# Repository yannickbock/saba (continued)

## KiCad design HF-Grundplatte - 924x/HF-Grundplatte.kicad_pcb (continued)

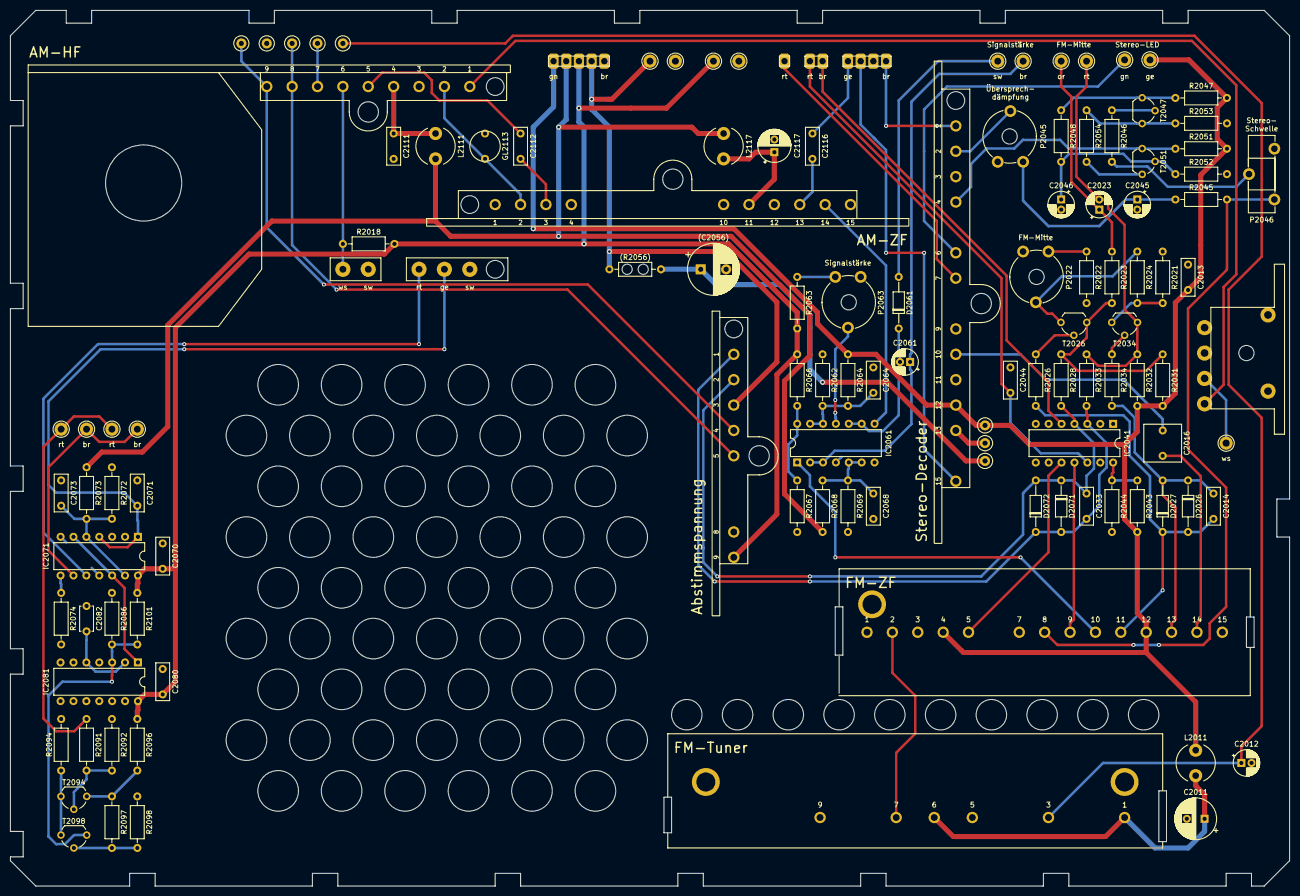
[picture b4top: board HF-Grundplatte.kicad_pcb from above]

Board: 2 copper layers, 252.0 x 172.5 mm, 120 parts (0 on the bottom side), 79 nets.

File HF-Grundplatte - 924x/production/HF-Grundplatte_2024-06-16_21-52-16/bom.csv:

Designator,Footprint,Quantity,Value,LCSC Part #
"_2, ",e9502d42-3ef4-4c54-9284-00e123373677,2,,
C2011,CP_Radial_D8.0mm_P3.50mm,1,220µ,
C2012,CP_Radial_D5.0mm_P2.00mm,1,2.2µ,
"C2013, C2014, C2044, C2064, C2068, C2070, C2071, C2073, C2080, C2111, C2112, C2116",C_Rect_L7.2mm_W2.5mm_P5.00mm_FKS2_FKP2_MKS2_MKP2,12,100n,
C2016,C_Rect_L7.2mm_W7.2mm_P5.00mm_FKS2_FKP2_MKS2_MKP2,1,2.2µ,
"C2023, C2061",CP_Radial_D5.0mm_P2.00mm,2,47µ,
C2033,C_Rect_L7.2mm_W2.5mm_P5.00mm_FKS2_FKP2_MKS2_MKP2,1,680n,
C2045,CP_Radial_D5.0mm_P2.00mm,1,22µ,
C2046,CP_Radial_D5.0mm_P2.00mm,1,4.7µ,
C2056,CP_Radial_D10.0mm_P5.00mm,1,100µ,
C2082,C_Disc_D4.7mm_W2.5mm_P5.00mm,1,22n,
C2117,CP_Radial_D6.3mm_P2.50mm,1,100µ,
"D2026, D2027, D2071, D2072",D_DO-35_SOD27_P10.16mm_Horizontal,4,1N4148,
D2061,D_DO-35_SOD27_P10.16mm_Horizontal,1,AA143,
GL2113,Glimmlampe,1,110V/0.6mA,
"IC2041, IC2061, IC2071",DIP-14_W7.62mm,3,4016,
IC2081,DIP-14_W7.62mm,1,4013,
J1,FM-Tuner,1,FM-Tuner,
"J10, J13, J26, J27, J9",Pin_D1.3mm_L11.0mm,5,br,
J11,Conn_01x04,1,NF,
J12,Conn_01x05,1,Power,
"J14, J34, J35, J36, J37",Pin_D1.3mm_L11.0mm,5,sw,
J15,Pin_D1.3mm_L11.0mm,1,rt,
J16,Pin_D1.3mm_L11.0mm,1,or,
J17,Pin_D1.3mm_L11.0mm,1,gn,
J18,Pin_D1.3mm_L11.0mm,1,ge,
J19,Conn_01x01,1,rt,
J2,AM-HF,1,AM-HF,
J20,SolderPads_Bridge_01x03_2.5mm,1,Conn_01x03,
"J21, J22, J23, J24, J25",TestPoint_Loop_D1.80mm_Drill1.0mm_Beaded,5,rt,
J28,Conn_01x02_5mm,1,Conn_01x02,
J29,Conn_01x03_5mm,1,Conn_01x03,
J3,AM-ZF,1,AM-ZF,
J30,Conn_01x02,1,Conn_01x02,
J4,Stereo-Decoder,1,~,
J5,Abstimmspannung,1,~,
J6,FM-ZF,1,FM-ZF,
J7,AM-Antenne,1,Antenne,
J8,Pin_D1.3mm_L11.0mm,1,Conn_01x01,
"L2011, L2111, L2117",L_Radial_D7.5mm_P5.00mm_Fastron_07P,3,1000µH,
P2022,Potentiometer_Piher_PT-10-V10_Vertical,1,2.5k,
P2045,Potentiometer_Piher_PT-10-V10_Vertical,1,25k,
P2046,Potentiometer_Piher_PT-15-H05_Horizontal,1,100k,
P2063,Potentiometer_Piher_PT-10-V10_Vertical,1,10k,
R2018,R_Axial_DIN0207_L6.3mm_D2.5mm_P10.16mm_Horizontal,1,47k,
"R2021, R2031, R2032",R_Axial_DIN0207_L6.3mm_D2.5mm_P10.16mm_Horizontal,3,3.9k,
R2022,R_Axial_DIN0207_L6.3mm_D2.5mm_P10.16mm_Horizontal,1,2.7k,
"R2023, R2048, R2097",R_Axial_DIN0207_L6.3mm_D2.5mm_P10.16mm_Horizontal,3,15k,
R2024,R_Axial_DIN0207_L6.3mm_D2.5mm_P10.16mm_Horizontal,1,1k,
"R2026, R2034, R2047, R2052, R2098",R_Axial_DIN0207_L6.3mm_D2.5mm_P10.16mm_Horizontal,5,22k,
"R2028, R2033, R2045, R2067",R_Axial_DIN0207_L6.3mm_D2.5mm_P10.16mm_Horizontal,4,10k,
R2043,R_Axial_DIN0207_L6.3mm_D2.5mm_P10.16mm_Horizontal,1,2.2k,
R2044,R_Axial_DIN0207_L6.3mm_D2.5mm_P10.16mm_Horizontal,1,12k,
"R2046, R2066, R2086",R_Axial_DIN0207_L6.3mm_D2.5mm_P10.16mm_Horizontal,3,4.7k,
"R2051, R2101",R_Axial_DIN0207_L6.3mm_D2.5mm_P10.16mm_Horizontal,2,1.2k,
"R2053, R2094",R_Axial_DIN0207_L6.3mm_D2.5mm_P10.16mm_Horizontal,2,47,
R2054,R_Axial_DIN0207_L6.3mm_D2.5mm_P10.16mm_Horizontal,1,27,
R2056,R_Axial_DIN0207_L6.3mm_D2.5mm_P10.16mm_Horizontal,1,820,
"R2062, R2064, R2068, R2069, R2072, R2092",R_Axial_DIN0207_L6.3mm_D2.5mm_P10.16mm_Horizontal,6,100k,
"R2063, R2096",R_Axial_DIN0207_L6.3mm_D2.5mm_P10.16mm_Horizontal,2,5.6k,
"R2073, R2091",R_Axial_DIN0207_L6.3mm_D2.5mm_P10.16mm_Horizontal,2,33k,
R2074,R_Axial_DIN0207_L6.3mm_D2.5mm_P10.16mm_Horizontal,1,1.5k,
"T2026, T2034, T2047, T2051, T2094, T2098",TO-92_Wide,6,BC547,

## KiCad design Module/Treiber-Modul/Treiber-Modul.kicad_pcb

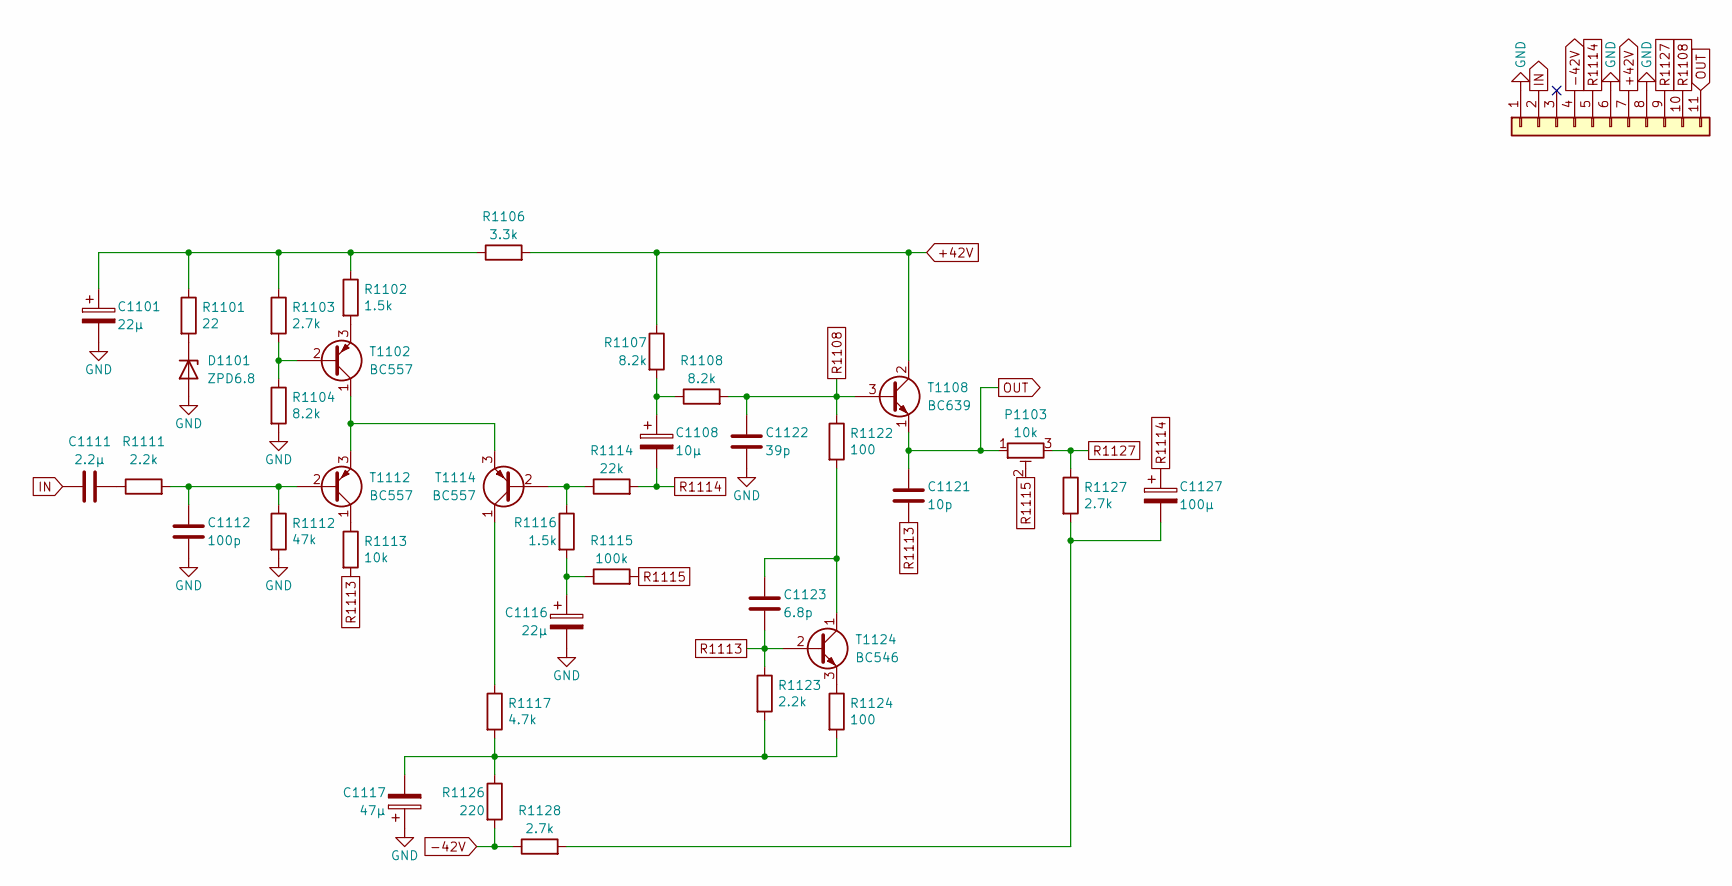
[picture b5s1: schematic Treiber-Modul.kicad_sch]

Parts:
C1101, C1116: 22µ; CP_Radial_D5.0mm_P2.00mm
C1108: 10µ; CP_Radial_D5.0mm_P2.00mm
C1111: 2.2µ; C_Rect_L7.2mm_W7.2mm_P5.00mm_FKS2_FKP2_MKS2_MKP2
C1112: 100p; C_Disc_D4.3mm_W1.9mm_P5.00mm
C1117: 47µ; CP_Radial_D8.0mm_P3.50mm
C1121: 10p; C_Disc_D4.3mm_W1.9mm_P5.00mm
C1122: 39p; C_Disc_D4.3mm_W1.9mm_P5.00mm
C1123: 6.8p; C_Disc_D4.3mm_W1.9mm_P5.00mm
C1127: 100µ; CP_Radial_D8.0mm_P3.50mm
D1101: ZPD6.8; D_DO-35_SOD27_P10.16mm_Horizontal
J1: Conn_01x13; Connector_01x11_5mm
P1103: 10k; Potentiometer_Piher_PT-10-H01_Horizontal
R1101: 22; R_Axial_DIN0207_L6.3mm_D2.5mm_P10.16mm_Horizontal
R1102, R1116: 1.5k; R_Axial_DIN0207_L6.3mm_D2.5mm_P10.16mm_Horizontal
R1103, R1127, R1128: 2.7k; R_Axial_DIN0207_L6.3mm_D2.5mm_P10.16mm_Horizontal
R1104, R1107, R1108: 8.2k; R_Axial_DIN0207_L6.3mm_D2.5mm_P10.16mm_Horizontal
R1106: 3.3k; R_Axial_DIN0411_L9.9mm_D3.6mm_P15.24mm_Horizontal
R1111, R1123: 2.2k; R_Axial_DIN0207_L6.3mm_D2.5mm_P10.16mm_Horizontal
R1112: 47k; R_Axial_DIN0207_L6.3mm_D2.5mm_P10.16mm_Horizontal
R1113: 10k; R_Axial_DIN0207_L6.3mm_D2.5mm_P10.16mm_Horizontal
R1114: 22k; R_Axial_DIN0207_L6.3mm_D2.5mm_P10.16mm_Horizontal
R1115: 100k; R_Axial_DIN0207_L6.3mm_D2.5mm_P10.16mm_Horizontal
R1117: 4.7k; R_Axial_DIN0207_L6.3mm_D2.5mm_P10.16mm_Horizontal
R1122, R1124: 100; R_Axial_DIN0207_L6.3mm_D2.5mm_P10.16mm_Horizontal
R1126: 220; R_Axial_DIN0207_L6.3mm_D2.5mm_P10.16mm_Horizontal
T1102, T1112, T1114: BC557; TO-92_Wide
T1108: BC639; TO-92_Wide
T1124: BC546; TO-92_Wide

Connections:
+42V: J1.7, R1106.2, R1107.1, T1108.2 (C)
-42V: J1.4, R1126.2, R1128.1
GND: C1101.2, C1112.2, C1116.2, C1117.1, C1122.2, D1101.2 (A), J1.1, J1.6, J1.8, R1104.2, R1112.2
IN: C1111.1, J1.2
unnamed: C1101.1, R1101.1, R1102.1, R1103.1, R1106.1
unnamed: C1108.1, R1107.2, R1108.1
unnamed: C1111.2, R1111.1
unnamed: C1116.1, R1115.1, R1116.2
unnamed: C1117.2, R1117.2, R1123.2, R1124.2, R1126.1
unnamed: C1127.2, R1127.2, R1128.2
unnamed: D1101.1 (K), R1101.2
unnamed: R1103.2, R1104.1, T1102.2 (B)
unnamed: T1102.1 (C), T1112.3 (E), T1114.3 (E)
unnamed: R1102.2, T1102.3 (E)
unnamed: C1112.1, R1111.2, R1112.1, T1112.2 (B)
unnamed: R1113.1, T1112.1 (C)
unnamed: R1114.1, R1116.1, T1114.2 (B)
unnamed: R1117.1, T1114.1 (C)
unnamed: C1123.1, R1122.2, T1124.1 (C)
unnamed: R1124.1, T1124.3 (E)
OUT: C1121.1, J1.11, P1103.1, T1108.1 (E)
R1108: C1122.1, J1.10, R1108.2, R1122.1, T1108.3 (B)
R1113: C1121.2, C1123.2, R1113.2, R1123.1, T1124.2 (B)
R1114: C1108.2, C1127.1, J1.5, R1114.2
R1115: P1103.2, R1115.2
R1127: J1.9, P1103.3, R1127.1

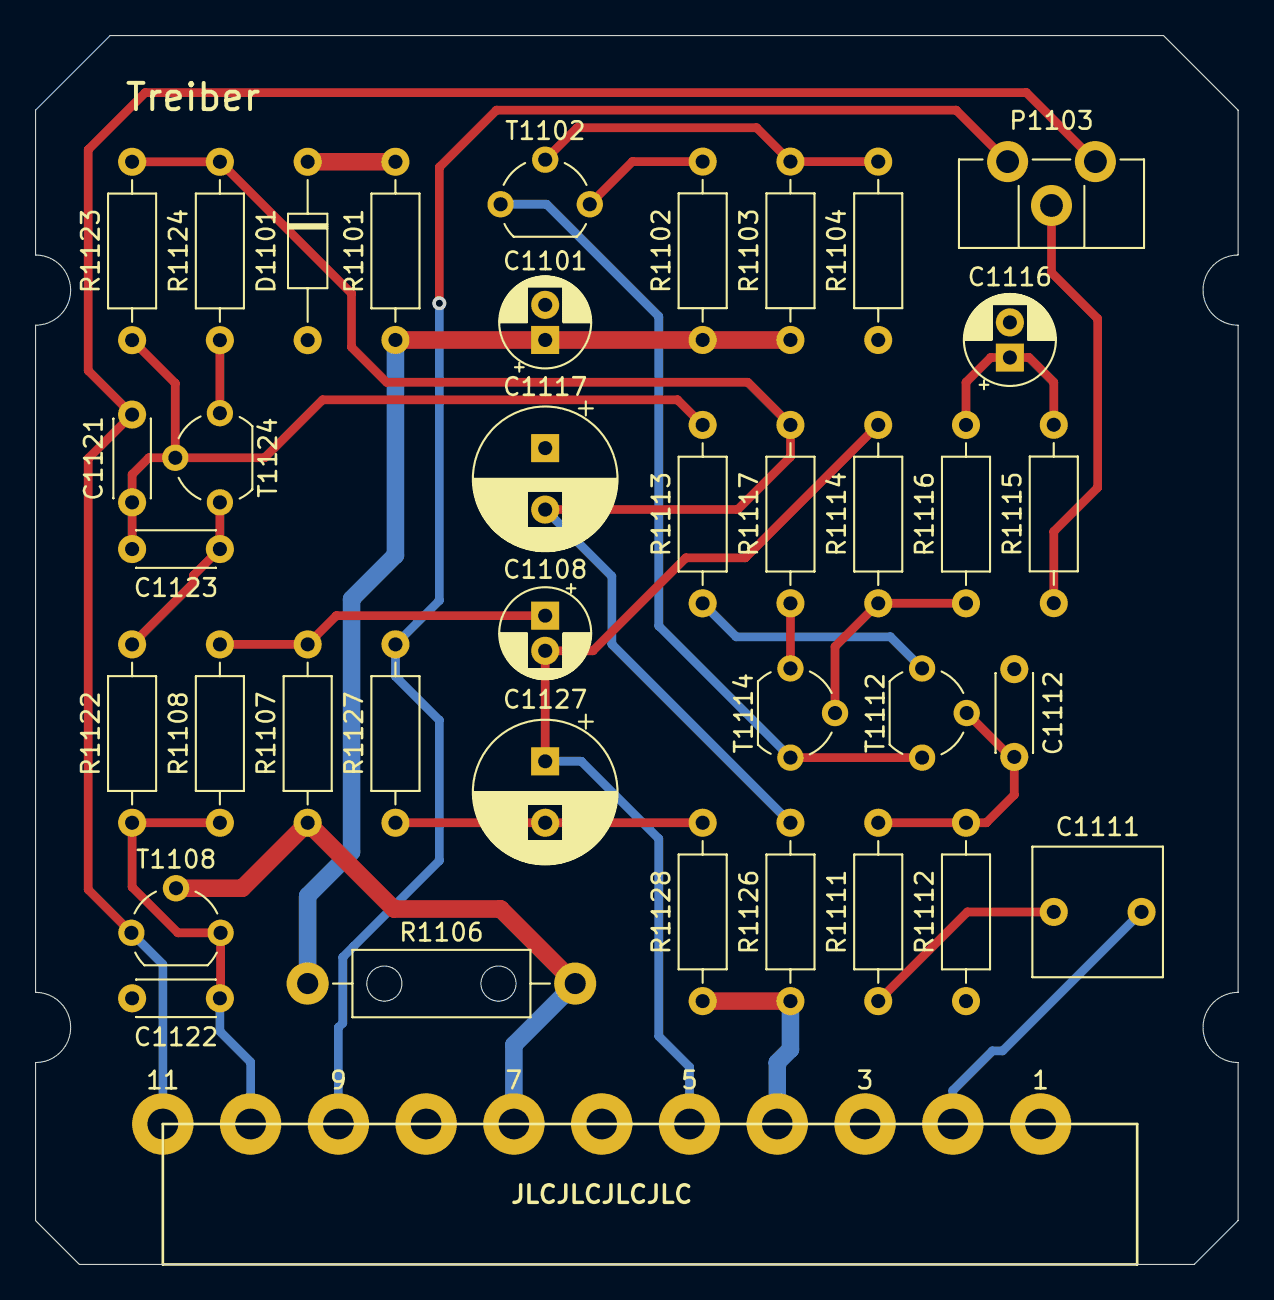
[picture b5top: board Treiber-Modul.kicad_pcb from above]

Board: 2 copper layers, 68.5 x 70.0 mm, 38 parts (0 on the bottom side), 26 nets.

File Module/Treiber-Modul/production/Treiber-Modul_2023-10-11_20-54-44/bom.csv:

Designator,Footprint,Quantity,Value,LCSC Part #
"C1101, C1116",CP_Radial_D5.0mm_P2.00mm,2,22µ,
C1108,CP_Radial_D5.0mm_P2.00mm,1,10µ,
C1111,C_Rect_L7.2mm_W7.2mm_P5.00mm_FKS2_FKP2_MKS2_MKP2,1,2.2µ,
C1112,C_Disc_D4.3mm_W1.9mm_P5.00mm,1,100p,
C1117,CP_Radial_D8.0mm_P3.50mm,1,47µ,
C1121,C_Disc_D4.3mm_W1.9mm_P5.00mm,1,10p,
C1122,C_Disc_D4.3mm_W1.9mm_P5.00mm,1,39p,
C1123,C_Disc_D4.3mm_W1.9mm_P5.00mm,1,6.8p,
C1127,CP_Radial_D8.0mm_P3.50mm,1,100µ,
D1101,D_DO-35_SOD27_P10.16mm_Horizontal,1,ZPD6.8,
J1,Connector_01x11_5mm,1,Conn_01x13,
P1103,Potentiometer_Piher_PT-10-H01_Horizontal,1,10k,
R1101,R_Axial_DIN0207_L6.3mm_D2.5mm_P10.16mm_Horizontal,1,22,
"R1102, R1116",R_Axial_DIN0207_L6.3mm_D2.5mm_P10.16mm_Horizontal,2,1.5k,
R1103,R_Axial_DIN0207_L6.3mm_D2.5mm_P10.16mm_Horizontal,1,2.7k,
R1104,R_Axial_DIN0207_L6.3mm_D2.5mm_P10.16mm_Horizontal,1,8.2k,
R1106,R_Axial_DIN0411_L9.9mm_D3.6mm_P15.24mm_Horizontal,1,3.3k,
"R1107, R1108",R_Axial_DIN0207_L6.3mm_D2.5mm_P10.16mm_Horizontal,2,8.2k,
"R1111, R1123",R_Axial_DIN0207_L6.3mm_D2.5mm_P10.16mm_Horizontal,2,2.2k,
R1112,R_Axial_DIN0207_L6.3mm_D2.5mm_P10.16mm_Horizontal,1,47k,
R1113,R_Axial_DIN0207_L6.3mm_D2.5mm_P10.16mm_Horizontal,1,10k,
R1114,R_Axial_DIN0207_L6.3mm_D2.5mm_P10.16mm_Horizontal,1,22k,
R1115,R_Axial_DIN0207_L6.3mm_D2.5mm_P10.16mm_Horizontal,1,100k,
R1117,R_Axial_DIN0207_L6.3mm_D2.5mm_P10.16mm_Horizontal,1,4.7k,
"R1122, R1124",R_Axial_DIN0207_L6.3mm_D2.5mm_P10.16mm_Horizontal,2,100,
R1126,R_Axial_DIN0207_L6.3mm_D2.5mm_P10.16mm_Horizontal,1,220,
"R1127, R1128",R_Axial_DIN0207_L6.3mm_D2.5mm_P10.16mm_Horizontal,2,2.7k,
"T1102, T1112, T1114",TO-92_Wide,3,BC557,
T1108,TO-92_Wide,1,BC639,
T1124,TO-92_Wide,1,BC546,

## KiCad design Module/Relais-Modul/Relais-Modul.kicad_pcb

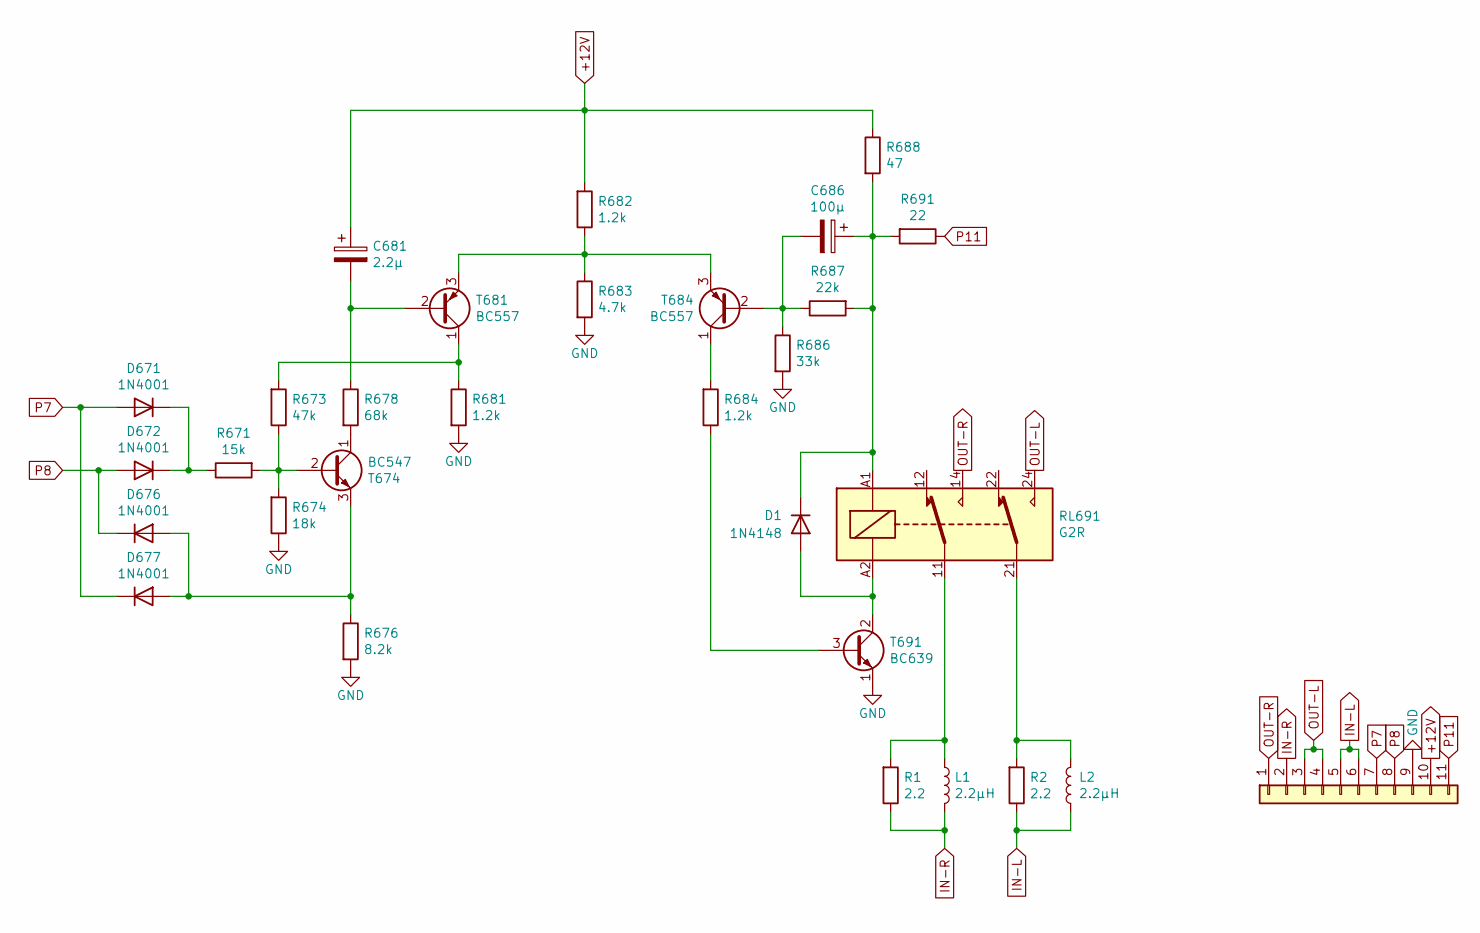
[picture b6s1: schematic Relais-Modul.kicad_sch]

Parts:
C681: 2.2µ; CP_Radial_D5.0mm_P2.50mm
C686: 100µ; CP_Radial_D6.3mm_P2.50mm
D1: 1N4148; D_DO-35_SOD27_P7.62mm_Horizontal
D671, D672, D676, D677: 1N4001; D_DO-41_SOD81_P10.16mm_Horizontal
J1: Conn_01x13; Connector_01x11_5mm
L1, L2: 2.2µH; L_Radial_D8.7mm_P5.00mm_Fastron_07HCP
R1, R2: 2.2; R_Axial_DIN0516_L15.5mm_D5.0mm_P7.62mm_Vertical
R671: 15k; R_Axial_DIN0207_L6.3mm_D2.5mm_P10.16mm_Horizontal
R673: 47k; R_Axial_DIN0207_L6.3mm_D2.5mm_P10.16mm_Horizontal
R674: 18k; R_Axial_DIN0207_L6.3mm_D2.5mm_P10.16mm_Horizontal
R676: 8.2k; R_Axial_DIN0207_L6.3mm_D2.5mm_P10.16mm_Horizontal
R678: 68k; R_Axial_DIN0207_L6.3mm_D2.5mm_P10.16mm_Horizontal
R681, R682, R684: 1.2k; R_Axial_DIN0207_L6.3mm_D2.5mm_P10.16mm_Horizontal
R683: 4.7k; R_Axial_DIN0207_L6.3mm_D2.5mm_P10.16mm_Horizontal
R686: 33k; R_Axial_DIN0207_L6.3mm_D2.5mm_P10.16mm_Horizontal
R687: 22k; R_Axial_DIN0207_L6.3mm_D2.5mm_P10.16mm_Horizontal
R688: 47; R_Axial_DIN0207_L6.3mm_D2.5mm_P10.16mm_Horizontal
R691: 22; R_Axial_DIN0207_L6.3mm_D2.5mm_P10.16mm_Horizontal
RL691: G2R; Relay_DPDT_Schrack-RT2_RM5mm
T674: BC547; TO-92_Wide
T681, T684: BC557; TO-92_Wide
T691: BC639; TO-92_Wide

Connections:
+12V: C681.1, J1.10, R682.2, R688.1
GND: J1.9, R674.1, R676.2, R681.2, R683.2, R686.2, T691.1 (E)
IN-L: J1.5, J1.6, L2.1, R2.1
IN-R: J1.2, L1.2, R1.1
unnamed: D1.2 (A), RL691.A2, T691.2 (C)
unnamed: C686.1, D1.1 (K), R687.2, R688.2, R691.2, RL691.A1
unnamed: D671.1 (K), D672.1 (K), R671.1
unnamed: D676.2 (A), D677.2 (A), R676.1, T674.3 (E)
unnamed: L1.1, R1.2, RL691.11
unnamed: L2.2, R2.2, RL691.21
unnamed: R671.2, R673.1, R674.2, T674.2 (B)
unnamed: R678.2, T674.1 (C)
unnamed: C681.2, R678.1, T681.2 (B)
unnamed: R673.2, R681.1, T681.1 (C)
unnamed: R682.1, R683.1, T681.3 (E), T684.3 (E)
unnamed: C686.2, R686.1, R687.1, T684.2 (B)
unnamed: R684.2, T684.1 (C)
unnamed: R684.1, T691.3 (B)
OUT-L: J1.3, J1.4, RL691.24
OUT-R: J1.1, RL691.14
P7: D671.2 (A), D677.1 (K), J1.7
P8: D672.2 (A), D676.1 (K), J1.8
P11: J1.11, R691.1

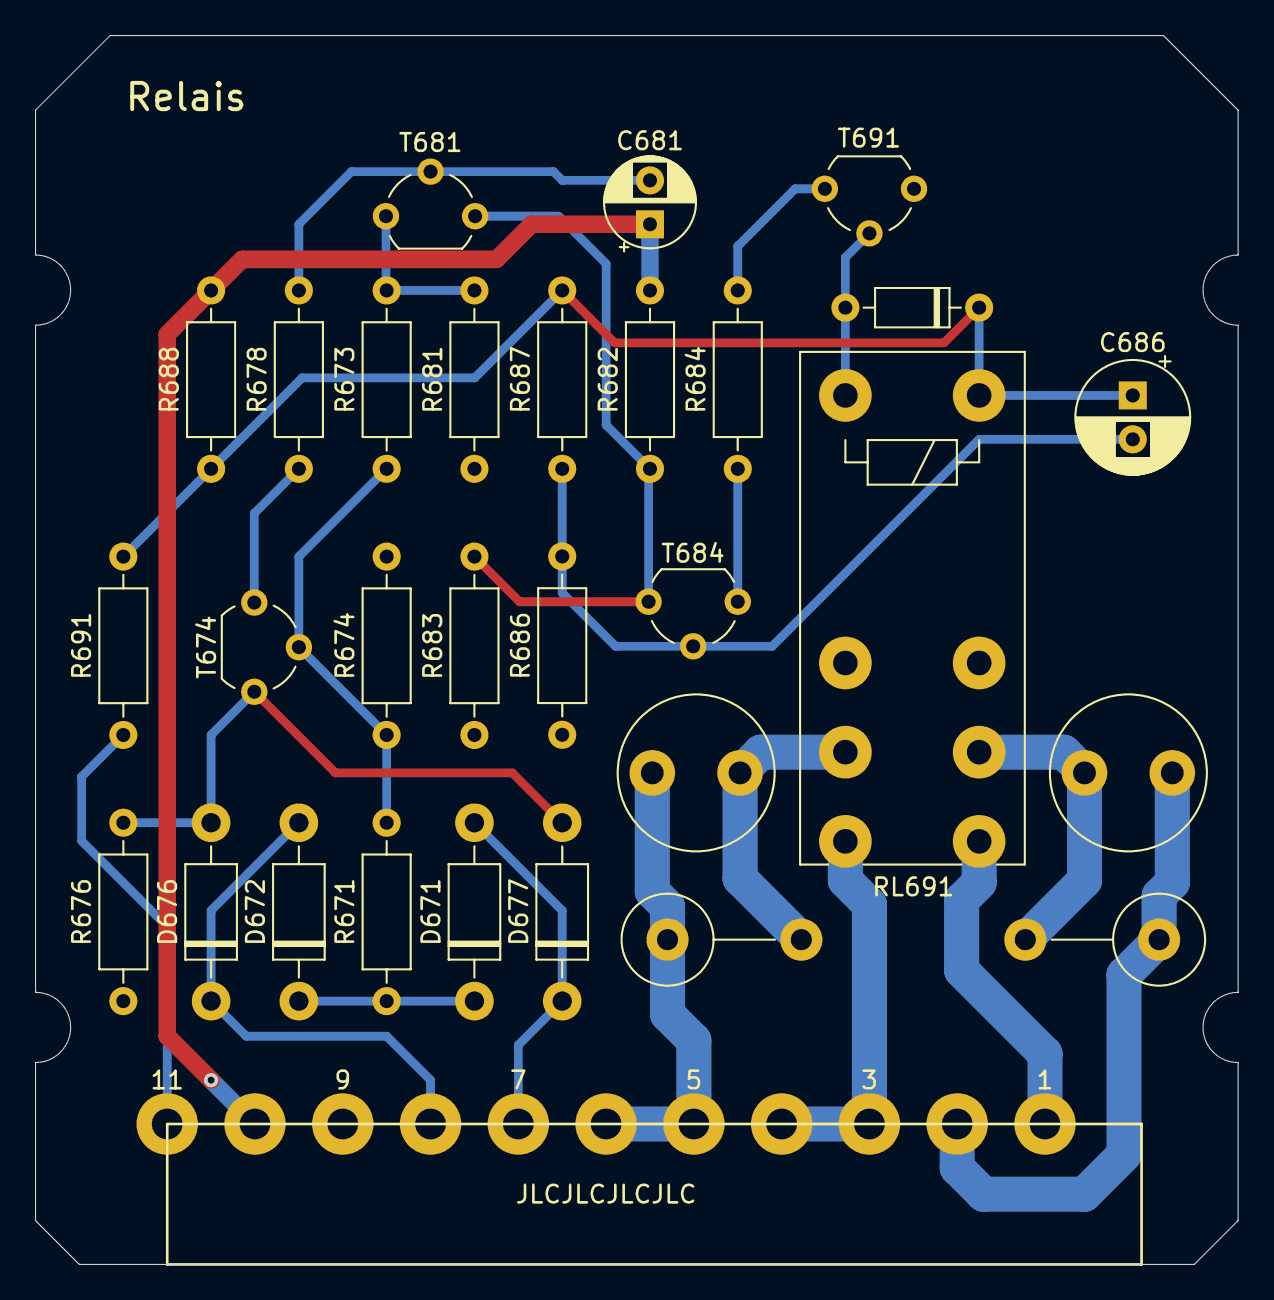
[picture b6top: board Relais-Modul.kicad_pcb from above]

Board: 2 copper layers, 68.5 x 70.0 mm, 30 parts (0 on the bottom side), 23 nets.

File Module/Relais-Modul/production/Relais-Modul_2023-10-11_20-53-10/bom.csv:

Designator,Footprint,Quantity,Value,LCSC Part #
C681,CP_Radial_D5.0mm_P2.50mm,1,2.2µ,
C686,CP_Radial_D6.3mm_P2.50mm,1,100µ,
D1,D_DO-35_SOD27_P7.62mm_Horizontal,1,1N4148,
"D671, D672, D676, D677",D_DO-41_SOD81_P10.16mm_Horizontal,4,1N4001,
J1,Connector_01x11_5mm,1,Conn_01x13,
"L1, L2",L_Radial_D8.7mm_P5.00mm_Fastron_07HCP,2,2.2µH,
"R1, R2",R_Axial_DIN0516_L15.5mm_D5.0mm_P7.62mm_Vertical,2,2.2,
R671,R_Axial_DIN0207_L6.3mm_D2.5mm_P10.16mm_Horizontal,1,15k,
R673,R_Axial_DIN0207_L6.3mm_D2.5mm_P10.16mm_Horizontal,1,47k,
R674,R_Axial_DIN0207_L6.3mm_D2.5mm_P10.16mm_Horizontal,1,18k,
R676,R_Axial_DIN0207_L6.3mm_D2.5mm_P10.16mm_Horizontal,1,8.2k,
R678,R_Axial_DIN0207_L6.3mm_D2.5mm_P10.16mm_Horizontal,1,68k,
"R681, R682, R684",R_Axial_DIN0207_L6.3mm_D2.5mm_P10.16mm_Horizontal,3,1.2k,
R683,R_Axial_DIN0207_L6.3mm_D2.5mm_P10.16mm_Horizontal,1,4.7k,
R686,R_Axial_DIN0207_L6.3mm_D2.5mm_P10.16mm_Horizontal,1,33k,
R687,R_Axial_DIN0207_L6.3mm_D2.5mm_P10.16mm_Horizontal,1,22k,
R688,R_Axial_DIN0207_L6.3mm_D2.5mm_P10.16mm_Horizontal,1,47,
R691,R_Axial_DIN0207_L6.3mm_D2.5mm_P10.16mm_Horizontal,1,22,
RL691,Relay_DPDT_Schrack-RT2_RM5mm,1,G2R,
T674,TO-92_Wide,1,BC547,
"T681, T684",TO-92_Wide,2,BC557,
T691,TO-92_Wide,1,BC639,

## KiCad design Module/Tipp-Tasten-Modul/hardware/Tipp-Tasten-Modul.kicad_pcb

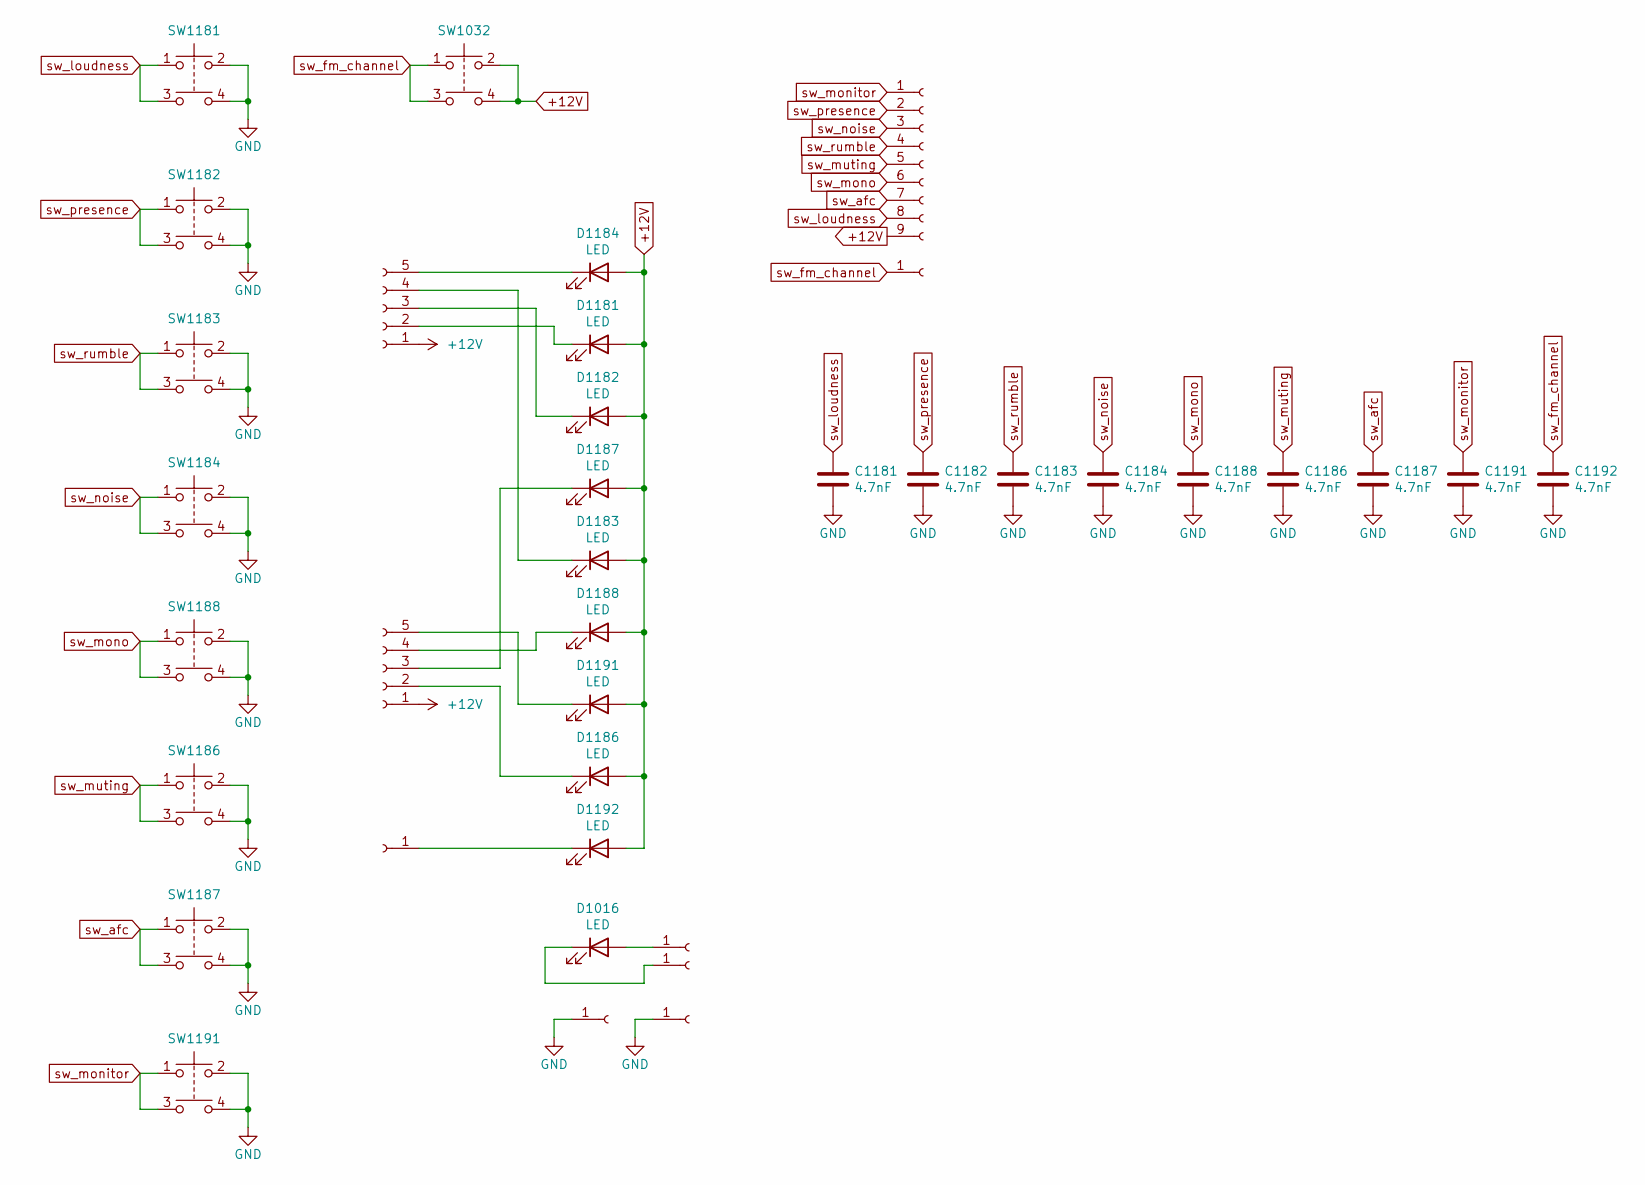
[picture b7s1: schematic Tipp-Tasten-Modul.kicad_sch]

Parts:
C1181, C1182, C1183, C1184, C1186, C1187, C1188, C1191, C1192: 4.7nF; C_Disc_D5.0mm_W2.5mm_P5.00mm
D1016: LED; LED_D5.0mm
D1181, D1182, D1183, D1184, D1186, D1187, D1188, D1191, D1192: LED; LED_D3.0mm
J1: Conn_01x09_Female; SolderWirePad_09_2.54mm
J2, J3: Conn_01x05_Female; SolderWirePad_05_2.54mm
J4, J5, J6, J8, J9, J10: Conn_01x01_Female; SolderWirePad_single_1-5mmDrill
SW1032: SW_Push_Dual; saba_92xx_push_button
SW1181, SW1182, SW1183, SW1184, SW1186, SW1187, SW1188, SW1191: SW_Push_Dual; SW_PUSH_DPDT

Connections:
+12V: D1181.2 (A), D1182.2 (A), D1183.2 (A), D1184.2 (A), D1186.2 (A), D1187.2 (A), D1188.2 (A), D1191.2 (A), D1192.2 (A), J1.9, J2.1, J3.1, SW1032.2, SW1032.4
GND: C1181.2, C1182.2, C1183.2, C1184.2, C1186.2, C1187.2, C1188.2, C1191.2, C1192.2, J6.1, J9.1, SW1181.2, SW1181.4, SW1182.2, SW1182.4, SW1183.2, SW1183.4, SW1184.2, SW1184.4, SW1186.2, SW1186.4, SW1187.2, SW1187.4, SW1188.2, SW1188.4, SW1191.2, SW1191.4
unnamed: D1016.1 (K), J10.1
unnamed: D1016.2 (A), J5.1
unnamed: D1181.1 (K), J3.2
unnamed: D1182.1 (K), J3.3
unnamed: D1183.1 (K), J3.4
unnamed: D1184.1 (K), J3.5
unnamed: D1186.1 (K), J2.2
unnamed: D1187.1 (K), J2.3
unnamed: D1188.1 (K), J2.4
unnamed: D1191.1 (K), J2.5
unnamed: D1192.1 (K), J8.1
sw_afc: C1187.1, J1.7, SW1187.1, SW1187.3
sw_fm_channel: C1192.1, J4.1, SW1032.1, SW1032.3
sw_loudness: C1181.1, J1.8, SW1181.1, SW1181.3
sw_monitor: C1191.1, J1.1, SW1191.1, SW1191.3
sw_mono: C1188.1, J1.6, SW1188.1, SW1188.3
sw_muting: C1186.1, J1.5, SW1186.1, SW1186.3
sw_noise: C1184.1, J1.3, SW1184.1, SW1184.3
sw_presence: C1182.1, J1.2, SW1182.1, SW1182.3
sw_rumble: C1183.1, J1.4, SW1183.1, SW1183.3

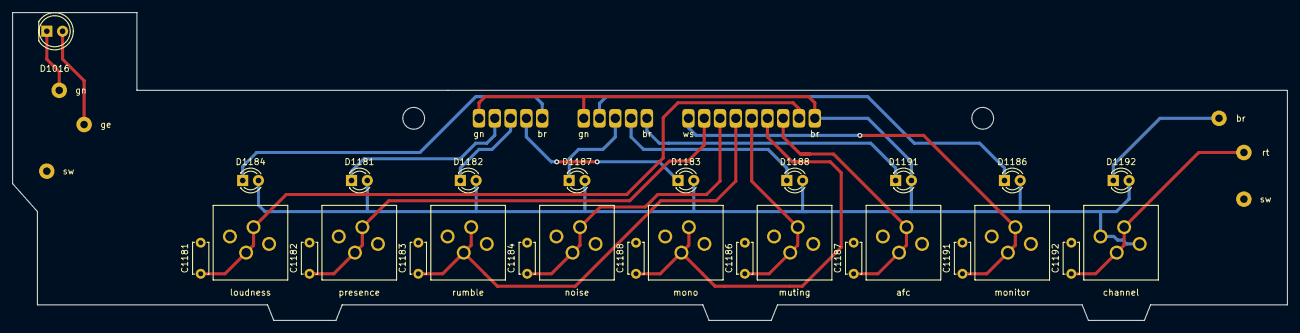
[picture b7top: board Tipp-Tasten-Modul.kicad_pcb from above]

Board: 2 copper layers, 205.0 x 49.5 mm, 39 parts (0 on the bottom side), 22 nets.

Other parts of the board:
M2, M3: MountingHole_3.5mm

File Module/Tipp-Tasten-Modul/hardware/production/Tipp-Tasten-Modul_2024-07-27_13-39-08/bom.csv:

Designator,Footprint,Quantity,Value,LCSC Part #
"C1181, C1182, C1183, C1184, C1186, C1187, C1188, C1191, C1192",C_Disc_D5.0mm_W2.5mm_P5.00mm,9,4.7nF,
D1016,LED_D5.0mm,1,LED,
"D1181, D1182, D1183, D1184, D1186, D1187, D1188, D1191, D1192",LED_D3.0mm,9,LED,
J1,Conn_01x09,1,Conn_01x09_Female,
"J10, J6, J8",SolderWirePad_single_1-5mmDrill,3,Conn_01x01_Female,
"J2, J3",Conn_01x05,2,Conn_01x05_Female,
"J4, J5",SolderWirePad_single_1-5mmDrill,2,Conn_01x01_Female,
"SW1032, SW1181, SW1182, SW1183, SW1184, SW1186, SW1187, SW1188, SW1191",SW__PUSH_DPDT,9,SW_Push_Dual,

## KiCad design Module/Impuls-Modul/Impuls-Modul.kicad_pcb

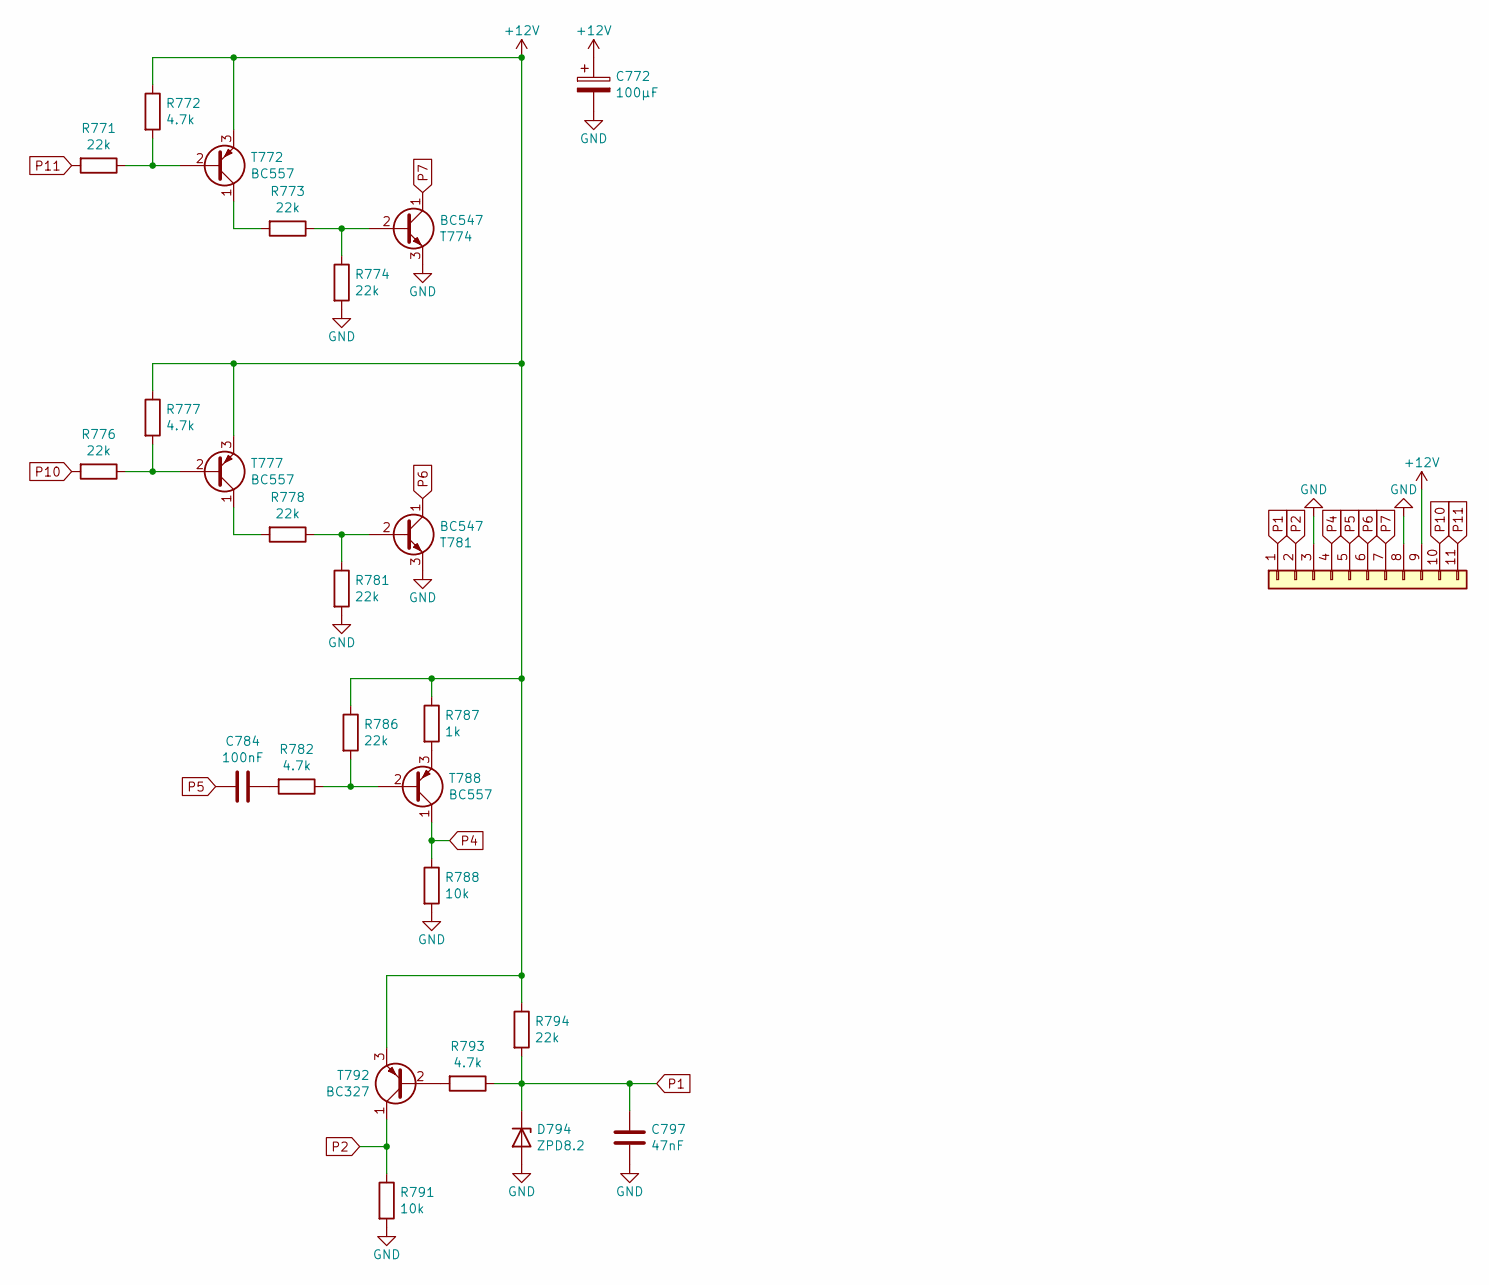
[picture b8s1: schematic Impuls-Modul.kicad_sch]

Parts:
C772: 100µF; CP_Radial_D6.3mm_P2.50mm
C784: 100nF; C_Rect_L7.0mm_W2.0mm_P5.00mm
C797: 47nF; C_Rect_L7.0mm_W2.0mm_P5.00mm
D794: ZPD8.2; D_DO-35_SOD27_P10.16mm_Horizontal
J1: Conn_01x13; Connector_01x11_5mm
R771, R773, R774, R776, R778, R781, R786, R794: 22k; R_Axial_DIN0207_L6.3mm_D2.5mm_P10.16mm_Horizontal
R772, R777, R782, R793: 4.7k; R_Axial_DIN0207_L6.3mm_D2.5mm_P10.16mm_Horizontal
R787: 1k; R_Axial_DIN0207_L6.3mm_D2.5mm_P10.16mm_Horizontal
R788, R791: 10k; R_Axial_DIN0207_L6.3mm_D2.5mm_P10.16mm_Horizontal
T772, T777, T788: BC557; TO-92_Wide
T774, T781: BC547; TO-92_Wide
T792: BC327; TO-92_Wide

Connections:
+12V: C772.1, J1.9, R772.1, R777.1, R786.1, R787.1, R794.1, T772.3 (E), T777.3 (E), T792.3 (E)
GND: C772.2, C797.2, D794.2 (A), J1.3, J1.8, R774.2, R781.2, R788.2, R791.2, T774.3 (E), T781.3 (E)
unnamed: C784.1, R782.2
unnamed: R771.1, R772.2, T772.2 (B)
unnamed: R773.2, T772.1 (C)
unnamed: R773.1, R774.1, T774.2 (B)
unnamed: R776.1, R777.2, T777.2 (B)
unnamed: R778.2, T777.1 (C)
unnamed: R778.1, R781.1, T781.2 (B)
unnamed: R782.1, R786.2, T788.2 (B)
unnamed: R787.2, T788.3 (E)
unnamed: R793.2, T792.2 (B)
P1: C797.1, D794.1 (K), J1.1, R793.1, R794.2
P2: J1.2, R791.1, T792.1 (C)
P4: J1.4, R788.1, T788.1 (C)
P5: C784.2, J1.5
P6: J1.6, T781.1 (C)
P7: J1.7, T774.1 (C)
P10: J1.10, R776.2
P11: J1.11, R771.2

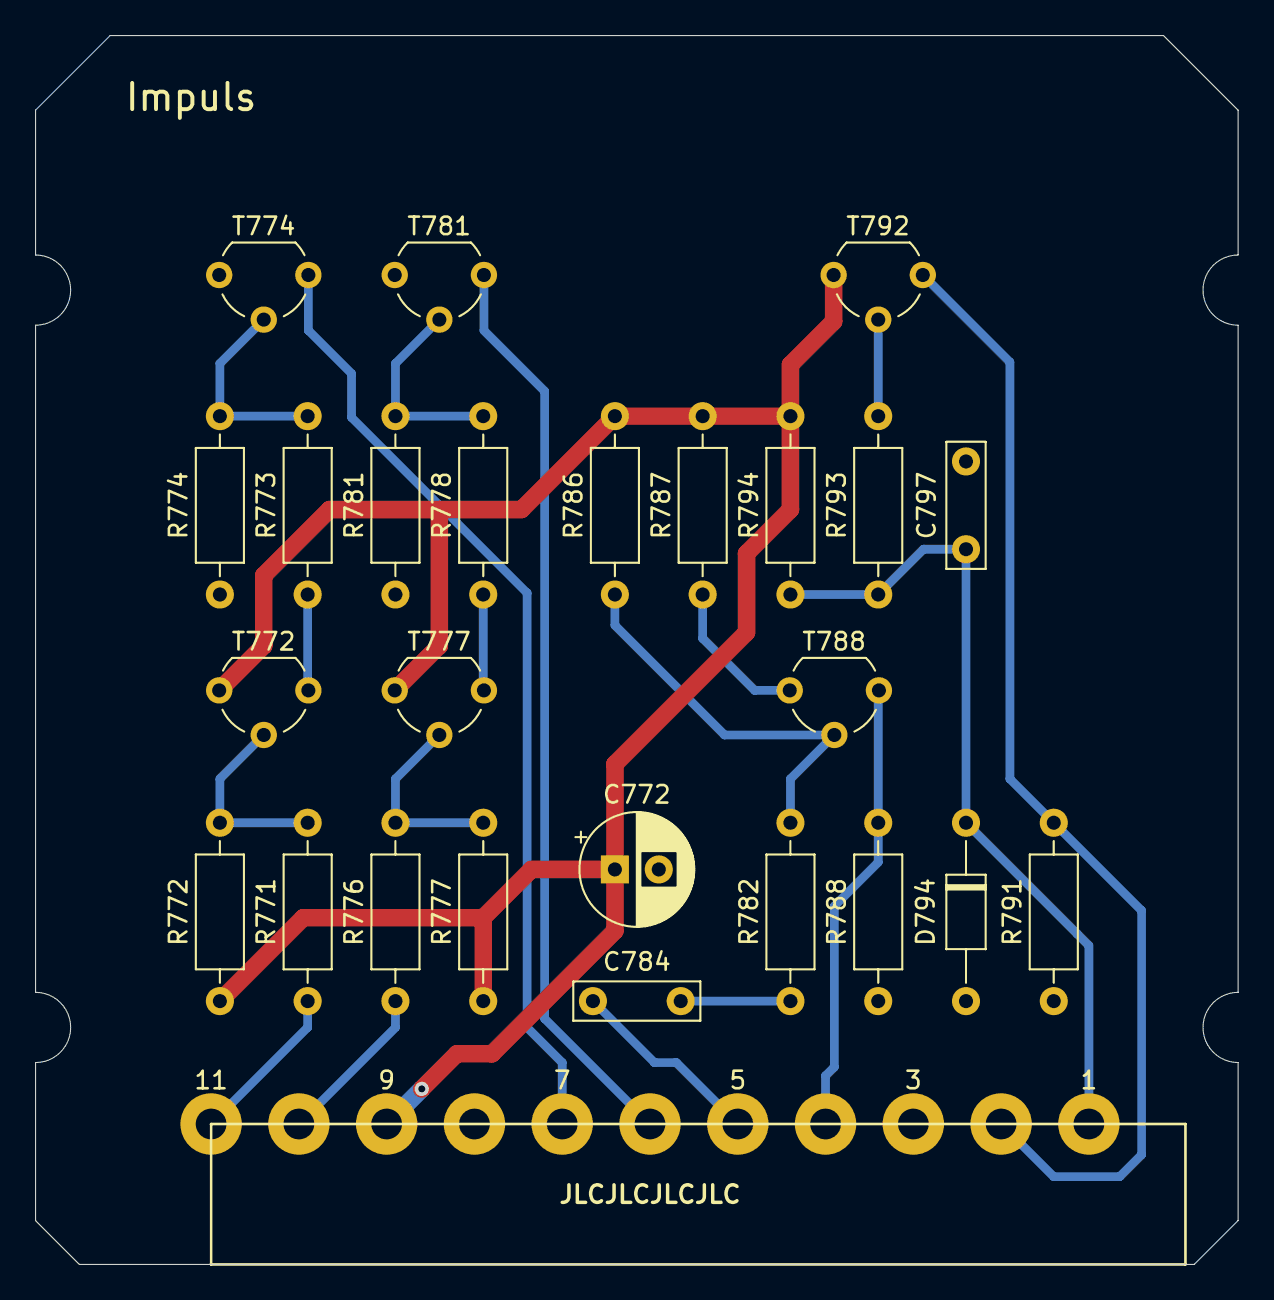
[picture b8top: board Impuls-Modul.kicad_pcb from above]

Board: 2 copper layers, 68.5 x 70.0 mm, 26 parts (0 on the bottom side), 20 nets.

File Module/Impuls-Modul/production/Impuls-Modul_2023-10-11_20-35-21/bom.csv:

Designator,Footprint,Quantity,Value,LCSC Part #
C772,CP_Radial_D6.3mm_P2.50mm,1,100µF,
C784,C_Rect_L7.0mm_W2.0mm_P5.00mm,1,100nF,
C797,C_Rect_L7.0mm_W2.0mm_P5.00mm,1,47nF,
D794,D_DO-35_SOD27_P10.16mm_Horizontal,1,ZPD8.2,
J1,Connector_01x11_5mm,1,Conn_01x13,
"R771, R773, R774, R776, R778, R781, R786, R794",R_Axial_DIN0207_L6.3mm_D2.5mm_P10.16mm_Horizontal,8,22k,
"R772, R777, R782, R793",R_Axial_DIN0207_L6.3mm_D2.5mm_P10.16mm_Horizontal,4,4.7k,
R787,R_Axial_DIN0207_L6.3mm_D2.5mm_P10.16mm_Horizontal,1,1k,
"R788, R791",R_Axial_DIN0207_L6.3mm_D2.5mm_P10.16mm_Horizontal,2,10k,
"T772, T777, T788",TO-92_Wide,3,BC557,
"T774, T781",TO-92_Wide,2,BC547,
T792,TO-92_Wide,1,BC327,

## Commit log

2022-05-13 Rev. A
2023-01-17 Some new stuff.
2024-03-22 A bunch of new modules added.
2024-07-06 HF- und NF-Grundplatte (924x) sowie AM-HF-Modul hinzugefügt.
2024-08-01 AZ553: LEDS added to BOM / Anzeige-Modul: Added additional Monting-Holes / Tipp-Tasten-Modul: Modified Push-Button Footprint
2024-08-08 Stereo-Decoder 4-Spulen / Anzeige-Modul überarbeitet
2024-08-14 AM-ZF-Modul
